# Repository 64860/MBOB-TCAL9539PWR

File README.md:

# 🚀 MBOB-TCAL9539PWR

<div align="center">

<!-- TODO: Add project logo (e.g., a render of the PCB) -->

 <!-- TODO: Add actual license -->

**A KiCad project for a main board design integrating the TCAL9539 16-bit I/O expander with power management considerations.**

</div>

## 📖 Overview

This repository contains the complete KiCad project files for the **MBOB-TCAL9539PWR**, a custom hardware design for a main board (MBOB) that heavily features the **TCAL9539 16-bit I2C/SMBus I/O expander**. The "PWR" in the name suggests an emphasis on power management, control, or monitoring capabilities, leveraging the I/O expander for additional control signals or status indications.

This project is ideal for hardware developers, electronics enthusiasts, and students looking to build upon a robust foundation for systems requiring extended general-purpose input/output and controlled power delivery, especially in embedded applications.

## ✨ Design Highlights & Features

-   **TCAL9539 I/O Expander Integration:** Central to the design, providing 16 additional I/O pins controllable via I2C/SMBus, suitable for various control and monitoring tasks.
-   **Comprehensive Schematic:** Detailed electrical diagram illustrating connectivity, components, and signal flow.
-   **Optimized PCB Layout:** Professional-grade Printed Circuit Board design, ready for manufacturing.
-   **3D Model Inclusion:** Incorporates a 3D model of a key connector (`SM04B-SRSS-TB`), aiding in mechanical integration and enclosure design.
-   **Power Management Ready:** The design likely includes components and traces tailored for robust power distribution or control, indicated by the "PWR" suffix and the I/O expander's potential use in such scenarios.
-   **Modular Backup System:** Includes a dedicated backup directory for project iteration safety.

## 🛠️ Tech Stack

**Electronic Design Automation (EDA):**
-   **KiCad:** The leading open-source EDA suite used for schematic capture and PCB layout.

**Key Components & Technologies:**
-   **TCAL9539:** Texas Instruments 16-bit I2C and SMBus I/O Expander.
    
-   **JST Connectors:** Likely used for power or signal interfaces (e.g., `SM04B-SRSS-TB`).

## 🚀 Getting Started

### Prerequisites

To open and work with this project, you will need:
-   **KiCad EDA Suite**: Version 7.0 or newer is recommended for full compatibility with the project files. You can download it from the [official KiCad website](https://www.kicad.org/download/).

### Installation & Project Setup

1.  **Clone the repository:**
    ```bash
    git clone https://github.com/64860/MBOB-TCAL9539PWR.git
    cd MBOB-TCAL9539PWR
    ```

2.  **Open the project in KiCad:**
    -   Launch KiCad.
    -   Go to `File > Open Project` (or `Project > Open Project` depending on your KiCad version).
    -   Navigate to the cloned `MBOB-TCAL9539PWR` directory and select `MBOB-TCAL9539PWR.kicad_pro`.

## 📁 Project Structure

```
MBOB-TCAL9539PWR/
├── Images/                         # Placeholder for project images, renders, or diagrams
├── MBOB-TCAL9539PWR-backups/       # Automated KiCad project backups
├── MBOB-TCAL9539PWR.kicad_pcb      # Main PCB layout file
├── MBOB-TCAL9539PWR.kicad_prl      # KiCad project local settings (e.g., display prefs)
├── MBOB-TCAL9539PWR.kicad_pro      # Main KiCad project file
├── MBOB-TCAL9539PWR.kicad_sch      # Main schematic capture file
├── SM04B-SRSS-TB(LF)(SN)--3DModel-STEP-269445.STEP # 3D model for a specific JST connector
├── fp-info-cache                   # KiCad's footprint information cache
├── tcal9539.pdf                    # Datasheet for the TCAL9539 I/O expander
└── README.md                       # This README file
```

## 🖥️ Viewing the Design

Once the project is open in KiCad:

-   **View Schematic:** Double-click `MBOB-TCAL9539PWR.kicad_sch` in the KiCad project manager to open the schematic editor.
-   **View PCB Layout:** Double-click `MBOB-TCAL9539PWR.kicad_pcb` in the KiCad project manager to open the PCB editor.
-   **View 3D Model of PCB:** Within the PCB editor, go to `View > 3D Viewer` to see a 3D render of the board.

## 📊 Generating Manufacturing Files

To send the PCB design for manufacturing, you will typically need to generate Gerber files, a Bill of Materials (BOM), and a Pick-and-Place file.

1.  **Gerber Files:**
    -   Open the PCB editor (`MBOB-TCAL9539PWR.kicad_pcb`).
    -   Go to `File > Plot`.
    -   Select "Gerber" as the Plot format and configure your desired layers and output directory.
    -   Click "Plot" to generate the Gerber files.
    -   Also, generate the drill files (`File > Generate Drill Files`).

2.  **Bill of Materials (BOM):**
    -   Open the schematic editor (`MBOB-TCAL9539PWR.kicad_sch`).
    -   Go to `Tools > Generate Bill of Materials`.
    -   You can use one of the default XSLT scripts or a custom one to generate the BOM in various formats (CSV, HTML, XML).

3.  **Pick-and-Place File:**
    -   Open the PCB editor (`MBOB-TCAL9539PWR.kicad_pcb`).
    -   Go to `File > Fabrication Outputs > Footprint Position (.pos) File`.
    -   Configure settings and generate the file.

## 📸 Screenshots

<!-- TODO: Add actual screenshots or 3D renders of the schematic and PCB layout from the Images directory or generate new ones. -->
<!-- Example:

_Schematic view of the MBOB-TCAL9539PWR_

_Top view of the PCB layout_

_3D render of the assembled PCB_
-->
Refer to the `Images/` directory for any included visual documentation of the design.

## 🤝 Contributing

We welcome contributions to improve this hardware design! If you have suggestions for enhancements, bug fixes in the design, or alternative component choices, please feel free to:

1.  **Fork the repository.**
2.  **Create a new branch** (`git checkout -b feature/your-feature-name`).
3.  **Make your changes** in KiCad.
4.  **Commit your changes** (`git commit -m 'feat: Add new feature'`).
5.  **Push to the branch** (`git push origin feature/your-feature-name`).
6.  **Open a Pull Request** detailing your changes.

Please ensure your KiCad version is compatible and any changes maintain design integrity.

## 📄 License

This project currently has **no explicit license defined**. Users are advised to contact the repository owner for clarification on usage rights.

See the [LICENSE](LICENSE) file for details once a license is added. <!-- TODO: Add a LICENSE file with a suitable open-source hardware license (e.g., CERN OHL, MIT) -->

## 🙏 Acknowledgments

-   **KiCad EDA Suite** for providing an incredible open-source platform for hardware design.
-   **Texas Instruments** for the TCAL9539 I/O expander.
-   **JST** for their reliable connectors.
-   The wider open-source hardware community for inspiration and resources.

## 📞 Support & Contact

-   🐛 Issues: [GitHub Issues](https://github.com/64860/MBOB-TCAL9539PWR/issues) - for bug reports or design-related questions.
-   📧 For direct inquiries, please contact the repository owner via their GitHub profile. <!-- TODO: Add a specific contact email if desired -->

---

<div align="center">

**⭐ Star this repo if you find this project helpful!**

Made with ❤️ by [64860](https://github.com/64860)

</div>

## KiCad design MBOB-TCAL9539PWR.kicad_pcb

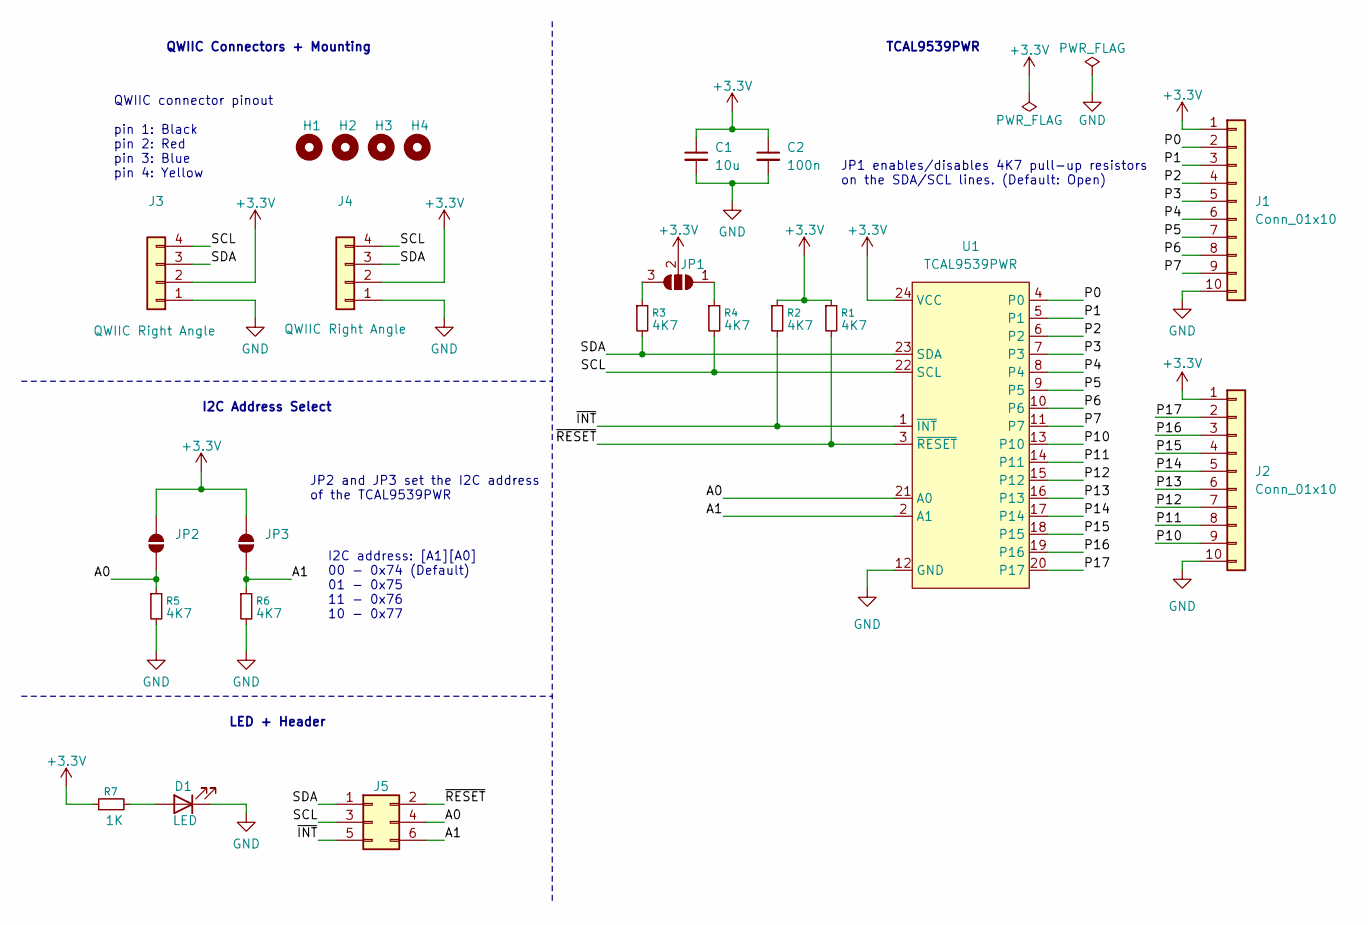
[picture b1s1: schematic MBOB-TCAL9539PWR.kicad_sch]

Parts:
C1: 10u; C_0603_1608Metric_Pad1.08x0.95mm_HandSolder
C2: 100n; C_0402_1005Metric_Pad0.74x0.62mm_HandSolder
D1: LED; LED_0603_1608Metric_Pad1.05x0.95mm_HandSolder
H1, H2, H3, H4: MountingHole; MountingHole_3.2mm_M3_DIN965_Pad
J1, J2: Conn_01x10; PinHeader_1x10_P2.54mm_Vertical
J3, J4: QWIIC Right Angle; JST_SH_SM04B-SRSS-TB_1x04-1MP_P1.00mm_Horizontal
J5: Conn_02x03_Odd_Even; PinHeader_2x03_P2.54mm_Vertical
JP1: SolderJumper_3_Open; SolderJumper-3_P1.3mm_Open_RoundedPad1.0x1.5mm
JP2, JP3: SolderJumper_2_Open; SolderJumper-2_P1.3mm_Open_RoundedPad1.0x1.5mm
R1, R2, R3, R4, R5, R6: 4K7; R_0402_1005Metric_Pad0.72x0.64mm_HandSolder
R7: 1K; R_0402_1005Metric_Pad0.72x0.64mm_HandSolder
U1: TCAL9539PWR; TSSOP-24_4.4x6.5mm_P0.5mm

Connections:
+3.3V: C1.1, C2.1, J1.1, J2.1, J3.2, J4.2, JP1.2 (C), JP2.2 (B), JP3.2 (B), R1.1, R2.1, R7.1, U1.24 (VCC)
/A0: J5.4, JP2.1 (A), R5.1, U1.21 (A0)
/A1: J5.6, JP3.1 (A), R6.1, U1.2 (A1)
/P0: J1.2, U1.4 (P0)
/P1: J1.3, U1.5 (P1)
/P2: J1.4, U1.6 (P2)
/P3: J1.5, U1.7 (P3)
/P4: J1.6, U1.8 (P4)
/P5: J1.7, U1.9 (P5)
/P6: J1.8, U1.10 (P6)
/P7: J1.9, U1.11 (P7)
/P10: J2.9, U1.13 (P10)
/P11: J2.8, U1.14 (P11)
/P12: J2.7, U1.15 (P12)
/P13: J2.6, U1.16 (P13)
/P14: J2.5, U1.17 (P14)
/P15: J2.4, U1.18 (P15)
/P16: J2.3, U1.19 (P16)
/P17: J2.2, U1.20 (P17)
/SCL: J3.4, J4.4, J5.3, R4.2, U1.22 (SCL)
/SDA: J3.3, J4.3, J5.1, R3.2, U1.23 (SDA)
/~INT: J5.5, R2.2, U1.1 (~INT)
/~RESET: J5.2, R1.2, U1.3 (~RESET)
GND: C1.2, C2.2, D1.1 (K), J1.10, J2.10, J3.1, J4.1, R5.2, R6.2, U1.12 (GND)
unnamed: D1.2 (A), R7.2
unnamed: JP1.1 (A), R4.1
unnamed: JP1.3 (B), R3.1

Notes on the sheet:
I2C Address Select
TCAL9539PWR
JP2 and JP3 set the I2C address of the TCAL9539PWR
QWIIC connector pinout pin 1: Black pin 2: Red pin 3: Blue pin 4: Yellow
LED + Header
I2C address: [A1][A0] 00 - 0x74 (Default) 01 - 0x75 11 - 0x76 10 - 0x77
JP1 enables/disables 4K7 pull-up resistors on the SDA/SCL lines. (Default: Open)
QWIIC Connectors + Mounting

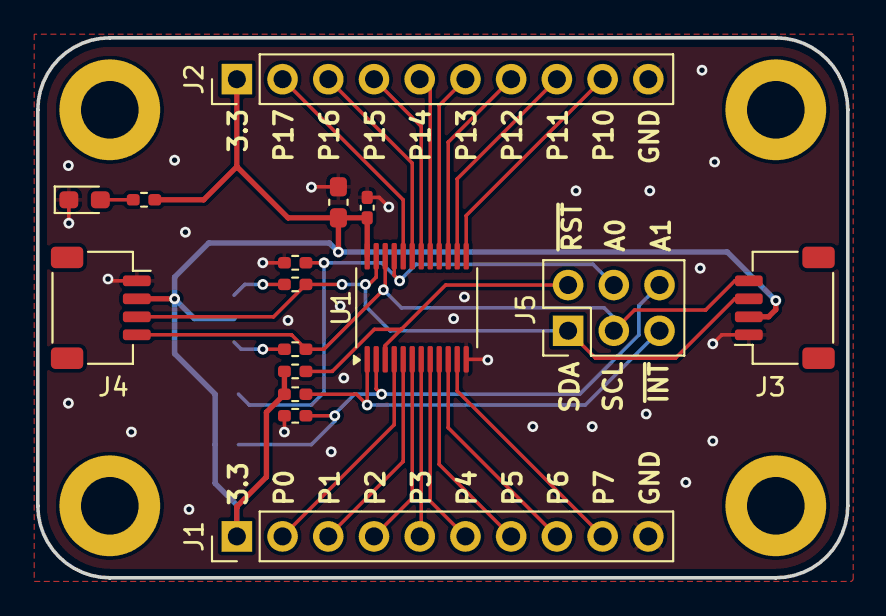
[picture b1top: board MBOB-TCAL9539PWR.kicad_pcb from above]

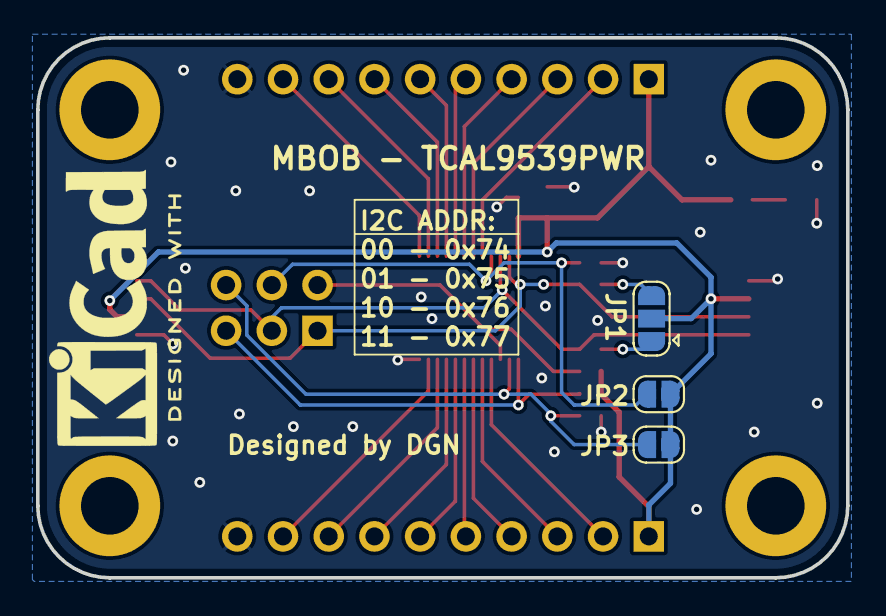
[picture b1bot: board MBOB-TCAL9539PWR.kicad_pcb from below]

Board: 2 copper layers, 45.0 x 30.0 mm, 23 parts (3 on the bottom side), 27 nets.

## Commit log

2026-01-07 Started my first commit. I designed the main symbol
2026-01-08 Finished drawing the schematics
2026-01-08 Added all the footprints
2026-02-17 Final commit
2026-02-17 Create README.md for MBOB-TCAL9539PWR project
    Add initial README with project overview and details.
2026-02-17 Revise README for clarity and project details
    Updated README to enhance project description and features.
